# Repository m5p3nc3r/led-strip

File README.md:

# led-strip

Trigger a rebuild...

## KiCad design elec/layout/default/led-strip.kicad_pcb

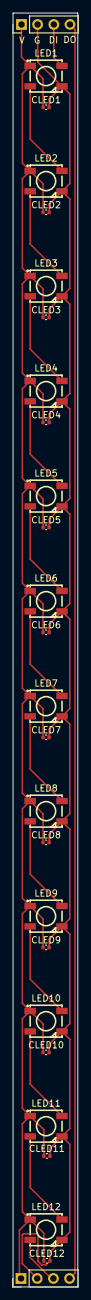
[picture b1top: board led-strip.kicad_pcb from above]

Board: 2 copper layers, 10.2 x 200.0 mm, 26 parts (0 on the bottom side), 16 nets.

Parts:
CLED1, CLED2, CLED3, CLED4, CLED5, CLED6, CLED7, CLED8, CLED9, CLED10, CLED11, CLED12: Multilayer Ceramic Capacitors MLCC - SMD/SMT 100n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; C0402
LED1, LED2, LED3, LED4, LED5, LED6, LED7, LED8, LED9, LED10, LED11, LED12: LED-SMD_4P-L5.0-W5.0-TL
U1, U2: PinHeader_1x04_P2.54mm_Vertical

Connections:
do: LED1.2, LED2.4
do-1: LED2.2, LED3.4
do-2: LED3.2, LED4.4
do-3: LED4.2, LED5.4
do-4: LED5.2, LED6.4
do-5: LED6.2, LED7.4
do-6: LED7.2, LED8.4
do-7: LED8.2, LED9.4
do-8: LED9.2, LED10.4
do-9: LED10.2, LED11.4
do-10: LED11.2, LED12.4
gnd: CLED1.2, CLED2.2, CLED3.2, CLED4.2, CLED5.2, CLED6.2, CLED7.2, CLED8.2, CLED9.2, CLED10.2, CLED11.2, CLED12.2, LED1.3, LED2.3, LED3.3, LED4.3, LED5.3, LED6.3, LED7.3, LED8.3, LED9.3, LED10.3, LED11.3, LED12.3, U1.2, U2.2
p3: LED1.4, U1.3
p3-1: LED12.2, U2.3
p4: U1.4, U2.4
vcc: CLED1.1, CLED2.1, CLED3.1, CLED4.1, CLED5.1, CLED6.1, CLED7.1, CLED8.1, CLED9.1, CLED10.1, CLED11.1, CLED12.1, LED1.1, LED2.1, LED3.1, LED4.1, LED5.1, LED6.1, LED7.1, LED8.1, LED9.1, LED10.1, LED11.1, LED12.1, U1.1, U2.1

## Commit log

2024-02-09 Initial checkin
2024-02-10 Change layout to be 10 pixels
2024-02-10 Trigger a rebuild
2024-02-10 Use a local copy of addressable-leds
    addressable-leds is not available in the repo yet
2024-02-11 change to 12 LED's per 20cm
